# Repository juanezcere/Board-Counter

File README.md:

# Board-Counter
Its an Eagle PCB design with a microcontroller to get information from a CANBUS protocol

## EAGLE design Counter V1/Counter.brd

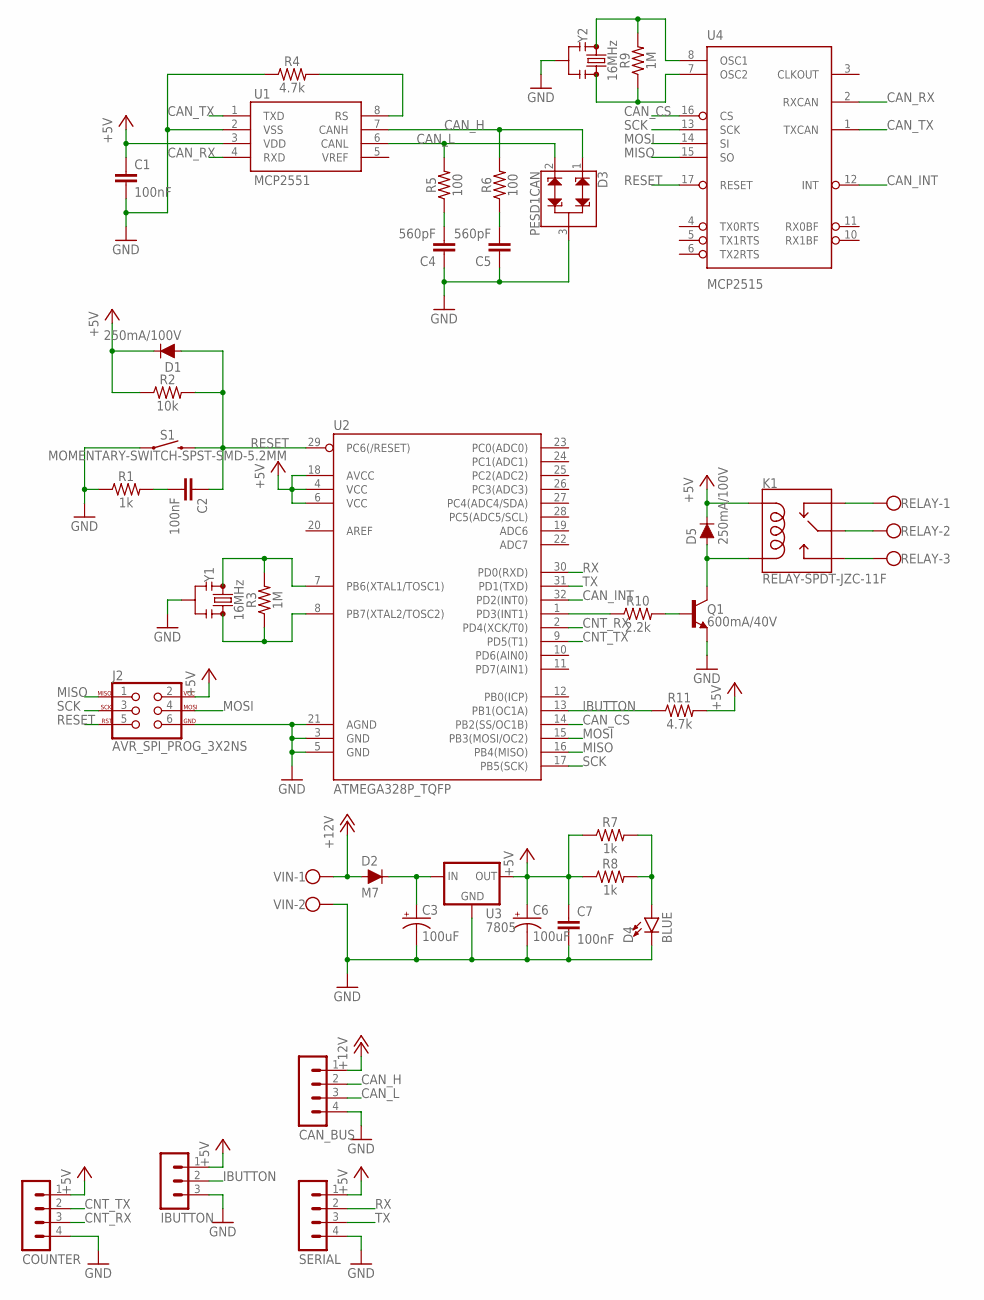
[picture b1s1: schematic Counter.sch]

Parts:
C1, C2, C7: 100nF; 0603
C3, C6: 100uF; PANASONIC_D
C4, C5: 560pF; 0603
CAN_BUS: MA04-1
COUNTER: MA04-1
D1, D5: 250mA/100V; SOD-323
D2: M7; SOD-323
D3: PESD1CAN; SOT23-3
D4: BLUE; LED-0603
IBUTTON: MA03-1
J2: AVR_SPI_PROG_3X2NS; 2X3-NS
K1: RELAY-SPDT-JZC-11F; RELAY-JZC
Q1: 600mA/40V; SOT23-3
R1, R7, R8: 1k; 0603
R2: 10k; 0603
R3, R9: 1M; 0603
R4, R11: 4.7k; 0603
R5, R6: 100; 0603
R10: 2.2k; 0603
RELAY: W237-103
S1: MOMENTARY-SWITCH-SPST-SMD-5.2MM; TACTILE_SWITCH_SMD_5.2MM
SERIAL: MA04-1
U1: MCP2551; SO08
U2: ATMEGA328P_TQFP; TQFP32-08
U3: 7805; TO-252
U4: MCP2515; SO18W
VIN: W237-102
Y1, Y2: 16MHz; RESONATOR-SMD-3.2X1.3

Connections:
+5V: C1.1, C6.+, C7.1, COUNTER.1, D1.C, D5.C, IBUTTON.1, J2.2, K1.5 (COIL1), R2.1, R7.1, R8.1, R11.2, SERIAL.1, U1.3 (VDD), U2.4 (VCC), U2.6 (VCC), U2.18 (AVCC), U3.2 (OUT), U4.18 (VDD)
+12V: CAN_BUS.1, D2.A, VIN.1
CAN_CS: U2.14 (PB2(SS/OC1B)), U4.16 (CS)
CAN_H: CAN_BUS.2, D3.1, R6.2, U1.7 (CANH)
CAN_INT: U2.32 (PD2(INT0)), U4.12 (INT)
CAN_L: CAN_BUS.3, D3.2, R5.2, U1.6 (CANL)
CAN_RX: U1.4 (RXD), U4.2 (RXCAN)
CAN_TX: U1.1 (TXD), U4.1 (TXCAN)
CNT_RX: COUNTER.3, U2.2 (PD4(XCK/T0))
CNT_TX: COUNTER.2, U2.9 (PD5(T1))
GND: C1.2, C3.-, C4.1, C5.1, C6.-, C7.2, CAN_BUS.4, COUNTER.4, D3.3, D4.C, IBUTTON.3, J2.6, Q1.2 (E), R1.1, R4.1, S1.1, SERIAL.4, U1.2 (VSS), U2.3 (GND), U2.5 (GND), U2.21 (AGND), U3.3 (GND), U4.9 (VSS), VIN.2, Y1.2, Y2.2
IBUTTON: IBUTTON.2, R11.1, U2.13 (PB1(OC1A))
MISO: J2.1, U2.16 (PB4(MISO)), U4.15 (SO)
MOSI: J2.4, U2.15 (PB3(MOSI/OC2)), U4.14 (SI)
unnamed: R3.1, U2.8 (PB7(XTAL2/TOSC2)), Y1.3
unnamed: C3.+, D2.C, U3.1 (IN)
unnamed: R3.2, U2.7 (PB6(XTAL1/TOSC1)), Y1.1
unnamed: D4.A, R7.2, R8.2
unnamed: R4.2, U1.8 (RS)
unnamed: C2.2, R1.2
unnamed: K1.4 (MAIN), RELAY.2
unnamed: C5.2, R6.1
unnamed: C4.2, R5.1
unnamed: K1.2 (NC), RELAY.1
unnamed: K1.3 (NO), RELAY.3
unnamed: Q1.1 (B), R10.2
unnamed: D5.A, K1.1 (COIL2), Q1.3 (C)
unnamed: R10.1, U2.1 (PD3(INT1))
unnamed: R9.1, U4.7 (OSC2), Y2.3
unnamed: R9.2, U4.8 (OSC1), Y2.1
RESET: C2.1, D1.A, J2.5, R2.2, S1.3 (2), U2.29 (PC6(/RESET)), U4.17 (RESET)
RX: SERIAL.2, U2.30 (PD0(RXD))
SCK: J2.3, U2.17 (PB5(SCK)), U4.13 (SCK)
TX: SERIAL.3, U2.31 (PD1(TXD))

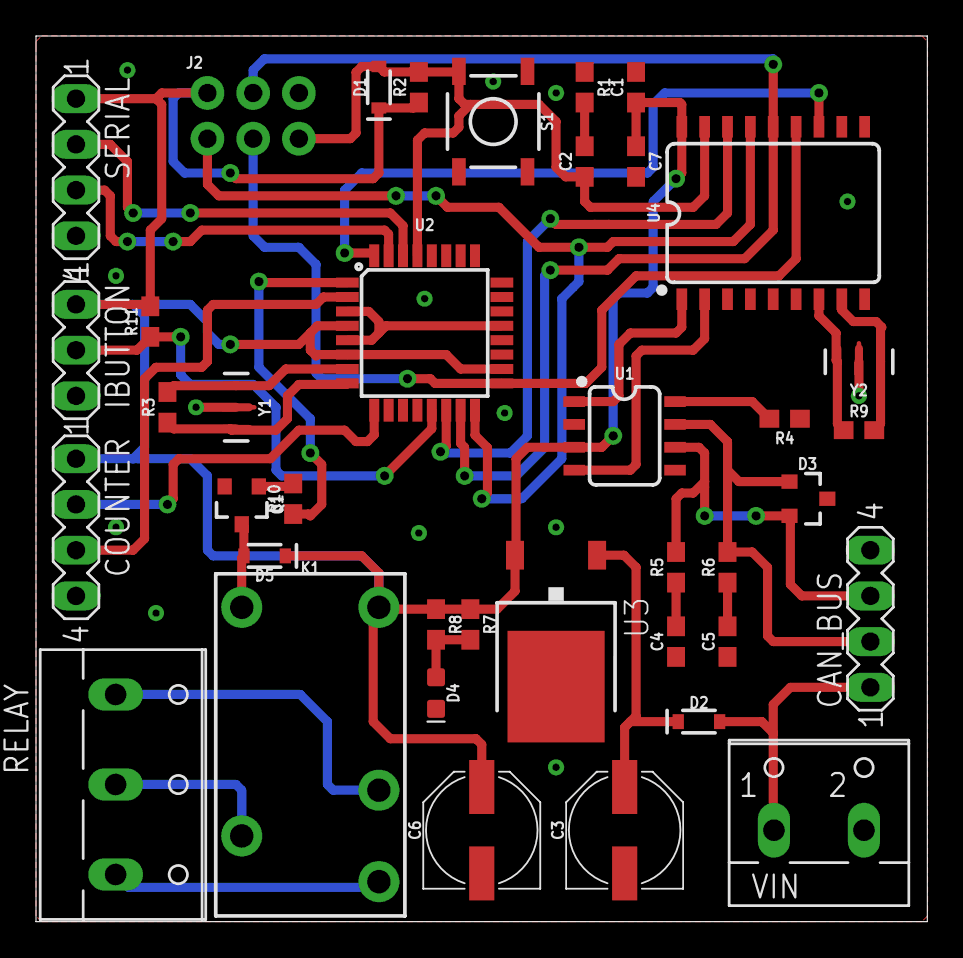
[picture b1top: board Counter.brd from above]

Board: 2 copper layers, 49.5 x 49.2 mm, 39 parts (0 on the bottom side), 34 nets.

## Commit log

2022-05-22 Upload of project

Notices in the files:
parts and their libraries:
SparkFun-Capacitors: Licensing: Creative Commons ShareAlike 4.0 International - https://creativecommons.org/licenses/by-sa/4.0
